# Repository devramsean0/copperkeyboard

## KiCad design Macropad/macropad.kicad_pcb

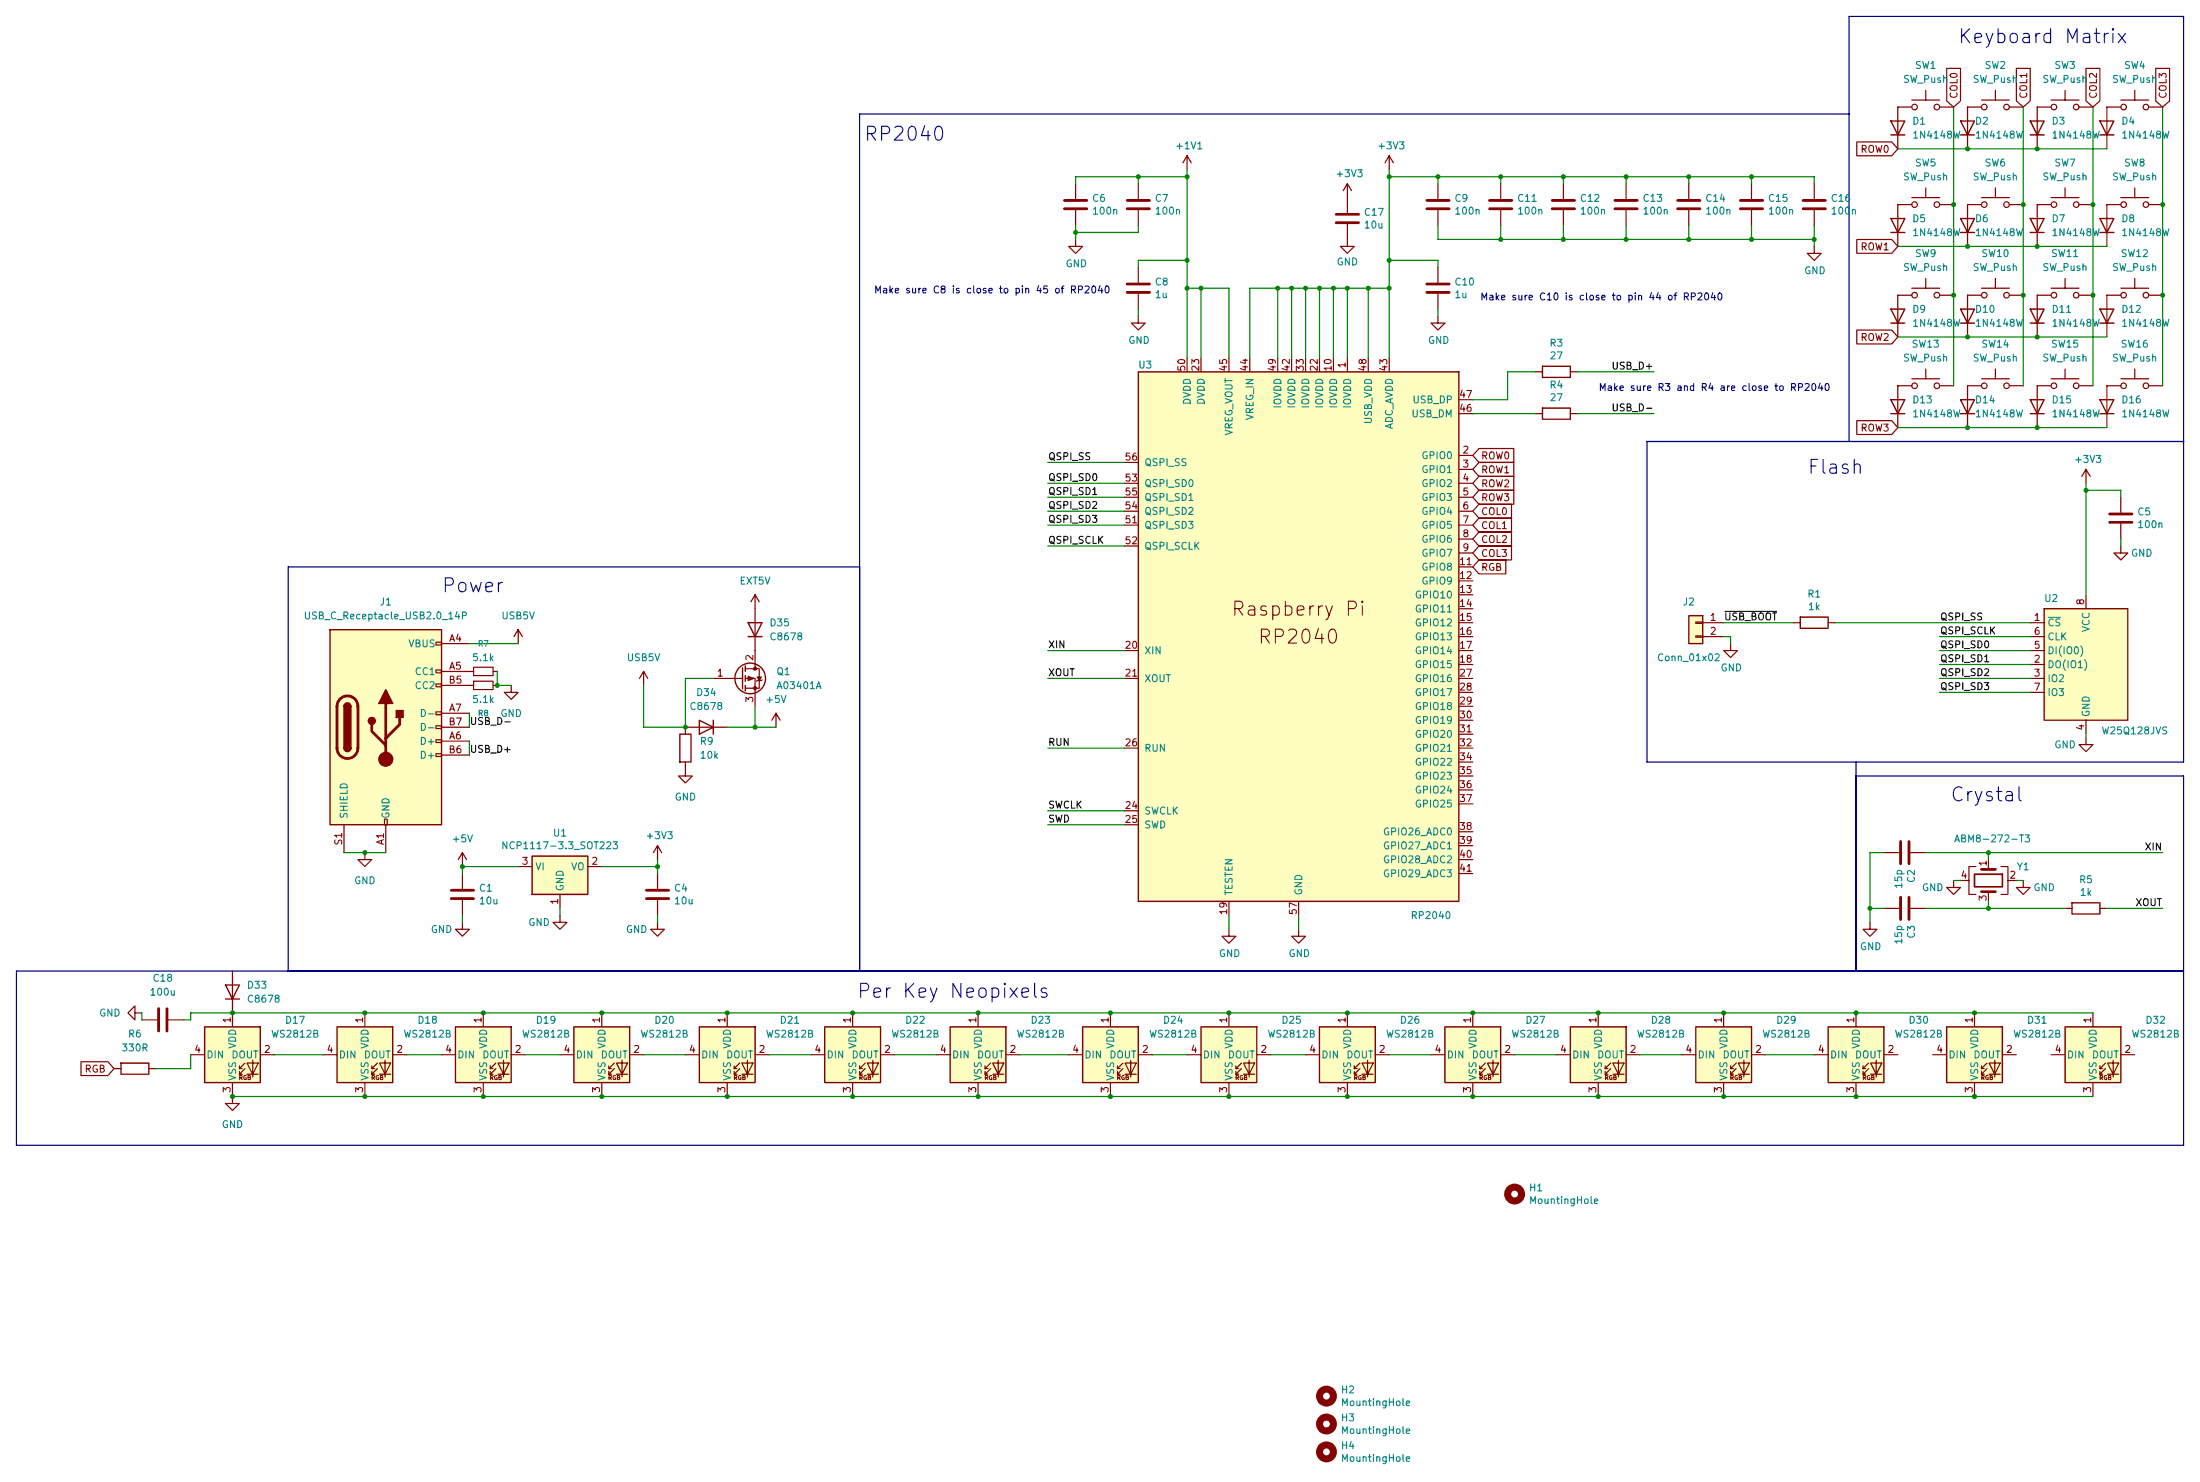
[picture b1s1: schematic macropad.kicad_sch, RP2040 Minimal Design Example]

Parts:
C1, C4, C17: 10u; C_0805_2012Metric
C2, C3: 15p; C_0402_1005Metric
C5, C6, C7, C9, C11, C12, C13, C14, C15, C16: 100n; C_0402_1005Metric
C8, C10: 1u; C_0402_1005Metric
C18: 100u; C_0805_2012Metric
D1, D2, D3, D4, D5, D6, D7, D8, D9, D10, D11, D12, D13, D14, D15, D16: 1N4148W; D_SOD-123
D17, D18, D19, D20, D21, D22, D23, D24, D25, D26, D27, D28, D29, D30, D31, D32: WS2812B; LED_WS2812B_PLCC4_5.0x5.0mm_P3.2mm
D33, D34, D35: C8678; D_SMA_Handsoldering
H1, H2, H3, H4: MountingHole; MountingHole_2.7mm_M2.5
J1: USB_C_Receptacle_USB2.0_14P; USB_C_Receptacle_G-Switch_GT-USB-7010ASV
J2: Conn_01x02; PinHeader_1x02_P2.54mm_Horizontal
Q1: A03401A; TO-252-2
R1, R5: 1k; R_0402_1005Metric
R3, R4: 27; R_0402_1005Metric
R6: 330R; R_0805_2012Metric
R7, R8: 5.1k; R_0805_2012Metric
R9: 10k; R_0805_2012Metric
SW1, SW2, SW3, SW4, SW5, SW6, SW7, SW8, SW9, SW10, SW11, SW12, SW13, SW14, SW15, SW16: SW_Push; Kailh-PG1353-Hotswap-1U
U1: NCP1117-3.3_SOT223; SOT-223-3_TabPin2
U2: W25Q128JVS; SOIC-8_5.23x5.23mm_P1.27mm
U3: RP2040; RP2040-QFN-56
Y1: ABM8-272-T3; Crystal_SMD_3225-4Pin_3.2x2.5mm

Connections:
+1V1: C6.1, C7.1, C8.1, U3.23 (DVDD), U3.45 (VREG_VOUT), U3.50 (DVDD)
+3V3: C4.1, C5.1, C9.1, C10.1, C11.1, C12.1, C13.1, C14.1, C15.1, C16.1, C17.1, U1.2 (VO), U2.8 (VCC), U3.1 (IOVDD), U3.10 (IOVDD), U3.22 (IOVDD), U3.33 (IOVDD), U3.42 (IOVDD), U3.43 (ADC_AVDD), U3.44 (VREG_IN), U3.48 (USB_VDD), U3.49 (IOVDD)
+5V: C1.1, D34.1 (K), Q1.3 (S), U1.3 (VI)
/QSPI_SCLK: U2.6 (CLK), U3.52 (QSPI_SCLK)
/QSPI_SD0: U2.5 (DI(IO0)), U3.53 (QSPI_SD0)
/QSPI_SD1: U2.2 (DO(IO1)), U3.55 (QSPI_SD1)
/QSPI_SD2: U2.3 (IO2), U3.54 (QSPI_SD2)
/QSPI_SD3: U2.7 (IO3), U3.51 (QSPI_SD3)
/QSPI_SS: R1.1, U2.1 (~CS), U3.56 (QSPI_SS)
/RUN: U3.26 (RUN)
/SWCLK: U3.24 (SWCLK)
/SWD: U3.25 (SWD)
/USB_D+: J1.A6 (D+), J1.B6 (D+), R3.1
/USB_D-: J1.A7 (D-), J1.B7 (D-), R4.1
/XIN: C2.1, U3.20 (XIN), Y1.1
/XOUT: R5.1, U3.21 (XOUT)
/~USB_BOOT: J2.1, R1.2
COL0: SW1.2, SW5.2, SW9.2, SW13.2, U3.6 (GPIO4)
COL1: SW2.2, SW6.2, SW10.2, SW14.2, U3.7 (GPIO5)
COL2: SW3.2, SW7.2, SW11.2, SW15.2, U3.8 (GPIO6)
COL3: SW4.2, SW8.2, SW12.2, SW16.2, U3.9 (GPIO7)
EXT5V: D35.2 (A)
GND: C1.2, C2.2, C3.2, C4.2, C5.2, C6.2, C7.2, C8.2, C9.2, C10.2, C11.2, C12.2, C13.2, C14.2, C15.2, C16.2, C17.2, C18.1, D17.3 (VSS), D18.3 (VSS), D19.3 (VSS), D20.3 (VSS), D21.3 (VSS), D22.3 (VSS), D23.3 (VSS), D24.3 (VSS), D25.3 (VSS), D26.3 (VSS), D27.3 (VSS), D28.3 (VSS), D29.3 (VSS), D30.3 (VSS), D31.3 (VSS), D32.3 (VSS), J1.A1 (GND), J1.A12 (GND), J1.B1 (GND), J1.B12 (GND), J1.S1 (SHIELD), J2.2, R7.2, R8.2, R9.2, U1.1 (GND), U2.4 (GND), U3.19 (TESTEN), U3.57 (GND), Y1.2, Y1.4
unnamed: C3.1, R5.2, Y1.3
unnamed: D1.2 (A), SW1.1
unnamed: D2.2 (A), SW2.1
unnamed: D3.2 (A), SW3.1
unnamed: D4.2 (A), SW4.1
unnamed: D5.2 (A), SW5.1
unnamed: D6.2 (A), SW6.1
unnamed: D7.2 (A), SW7.1
unnamed: D8.2 (A), SW8.1
unnamed: D9.2 (A), SW9.1
unnamed: D10.2 (A), SW10.1
unnamed: D11.2 (A), SW11.1
unnamed: D12.2 (A), SW12.1
unnamed: D13.2 (A), SW13.1
unnamed: D14.2 (A), SW14.1
unnamed: D15.2 (A), SW15.1
unnamed: D16.2 (A), SW16.1
unnamed: D17.4 (DIN), R6.1
unnamed: D17.2 (DOUT), D18.4 (DIN)
unnamed: C18.2, D17.1 (VDD), D18.1 (VDD), D19.1 (VDD), D20.1 (VDD), D21.1 (VDD), D22.1 (VDD), D23.1 (VDD), D24.1 (VDD), D25.1 (VDD), D26.1 (VDD), D27.1 (VDD), D28.1 (VDD), D29.1 (VDD), D30.1 (VDD), D31.1 (VDD), D32.1 (VDD), D33.1 (K)
unnamed: D18.2 (DOUT), D19.4 (DIN)
unnamed: D19.2 (DOUT), D20.4 (DIN)
unnamed: D20.2 (DOUT), D21.4 (DIN)
unnamed: D21.2 (DOUT), D22.4 (DIN)
unnamed: D22.2 (DOUT), D23.4 (DIN)
unnamed: D23.2 (DOUT), D24.4 (DIN)
unnamed: D24.2 (DOUT), D25.4 (DIN)
unnamed: D25.2 (DOUT), D26.4 (DIN)
unnamed: D26.2 (DOUT), D27.4 (DIN)
unnamed: D27.2 (DOUT), D28.4 (DIN)
unnamed: D28.2 (DOUT), D29.4 (DIN)
unnamed: D29.2 (DOUT), D30.4 (DIN)
unnamed: D35.1 (K), Q1.2 (D)
unnamed: J1.A5 (CC1), R7.1
unnamed: J1.B5 (CC2), R8.1
unnamed: R4.2, U3.46 (USB_DM)
unnamed: R3.2, U3.47 (USB_DP)
RGB: R6.2, U3.11 (GPIO8)
ROW0: D1.1 (K), D2.1 (K), D3.1 (K), D4.1 (K), U3.2 (GPIO0)
ROW1: D5.1 (K), D6.1 (K), D7.1 (K), D8.1 (K), U3.3 (GPIO1)
ROW2: D9.1 (K), D10.1 (K), D11.1 (K), D12.1 (K), U3.4 (GPIO2)
ROW3: D13.1 (K), D14.1 (K), D15.1 (K), D16.1 (K), U3.5 (GPIO3)
USB5V: D34.2 (A), J1.A4 (VBUS), J1.A9 (VBUS), J1.B4 (VBUS), J1.B9 (VBUS), Q1.1 (G), R9.1

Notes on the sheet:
Power
Crystal
Make sure C8 is close to pin 45 of RP2040
Per Key Neopixels
Make sure C10 is close to pin 44 of RP2040
RP2040
Make sure R3 and R4 are close to RP2040
Keyboard Matrix
Flash

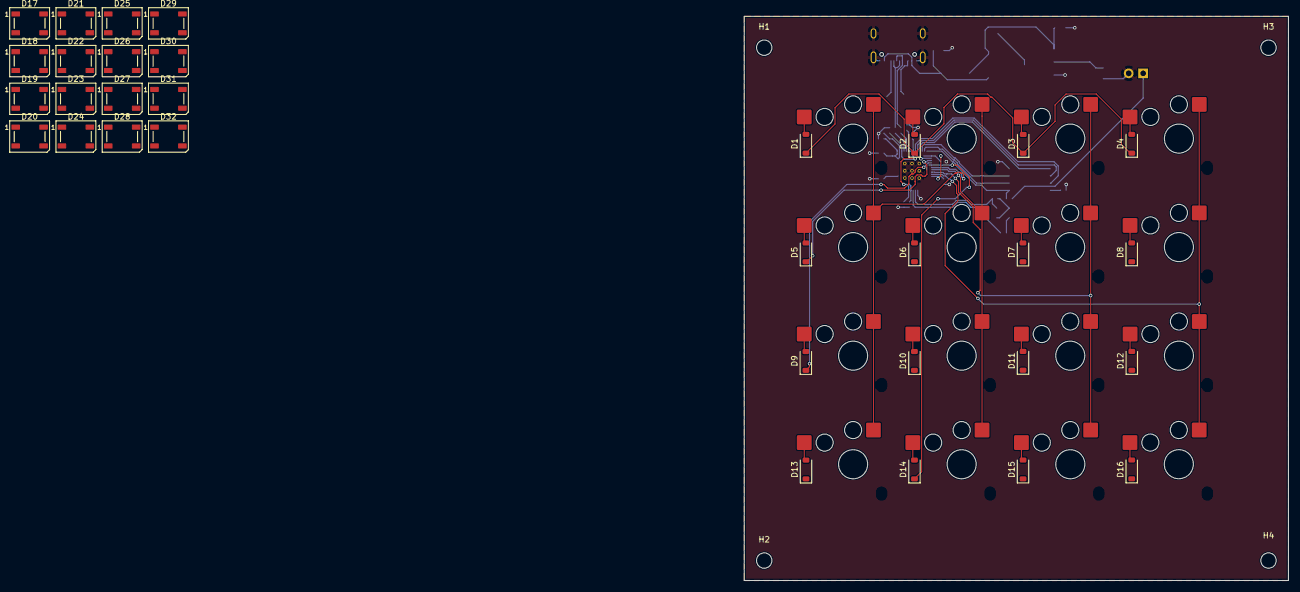
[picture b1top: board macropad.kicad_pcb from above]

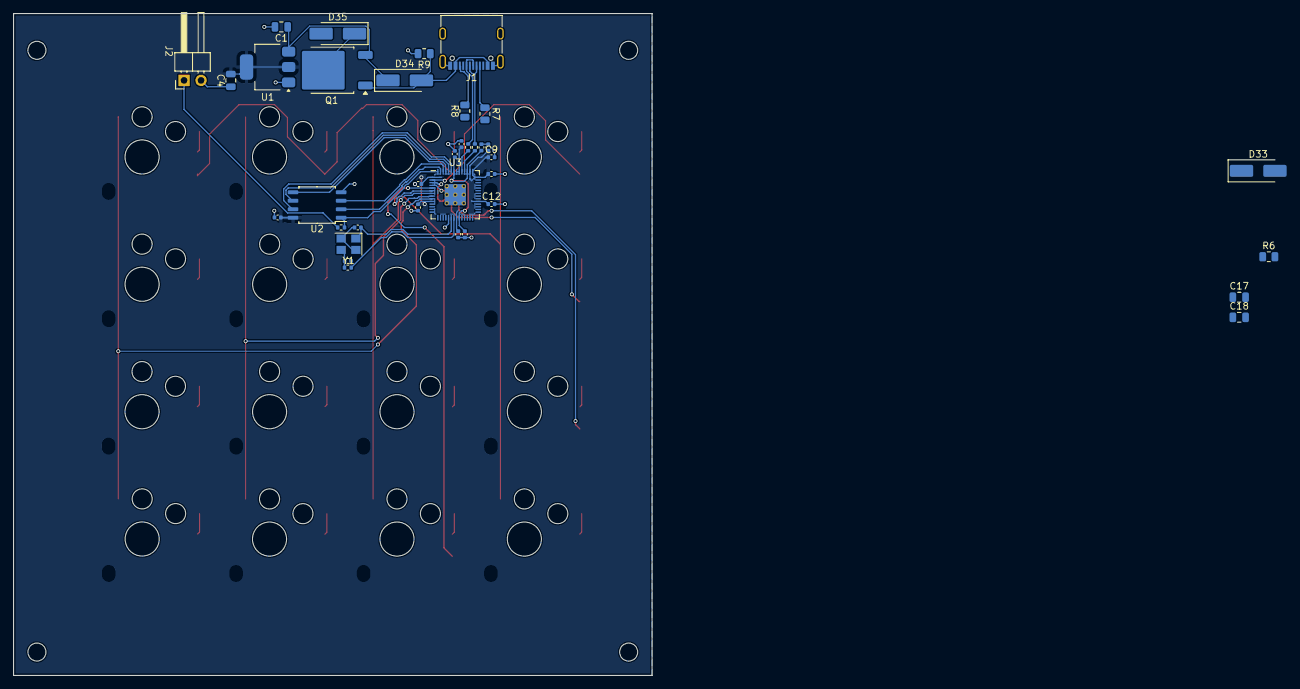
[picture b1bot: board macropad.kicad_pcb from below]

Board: 2 copper layers, 95.5 x 99.0 mm, 88 parts (36 on the bottom side), 62 nets.

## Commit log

2025-05-01 Some of a Macropad
2025-05-02 macropad: Finish routing - CommsBus - Neopixels
